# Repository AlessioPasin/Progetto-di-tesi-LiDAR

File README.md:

# Progetto di tesi: **Scheda per sensore LiDAR**

## Obiettivo:

Il seguente progetto riguarda una scheda per la gestione di due periferiche esterne: un laser ed un fotoricevitore.
L'obiettivo finale con la scheda è quello di realizzare un sensore LiDAR. Tale sensore viene utilizzato in diversi campi per misurare quella che è la distanza degli oggetti circostanti. Ne esistono di diverse tipologie e che sfruttano diversi principi fisici.

In questa applicazione viene utilizzato il **ToF** [*Time of Filght*], ossia il tempo che impiega il fascio laser per viaggare dalla sorgente all'oggetto e per poi tornare nuovamente alla fonte.

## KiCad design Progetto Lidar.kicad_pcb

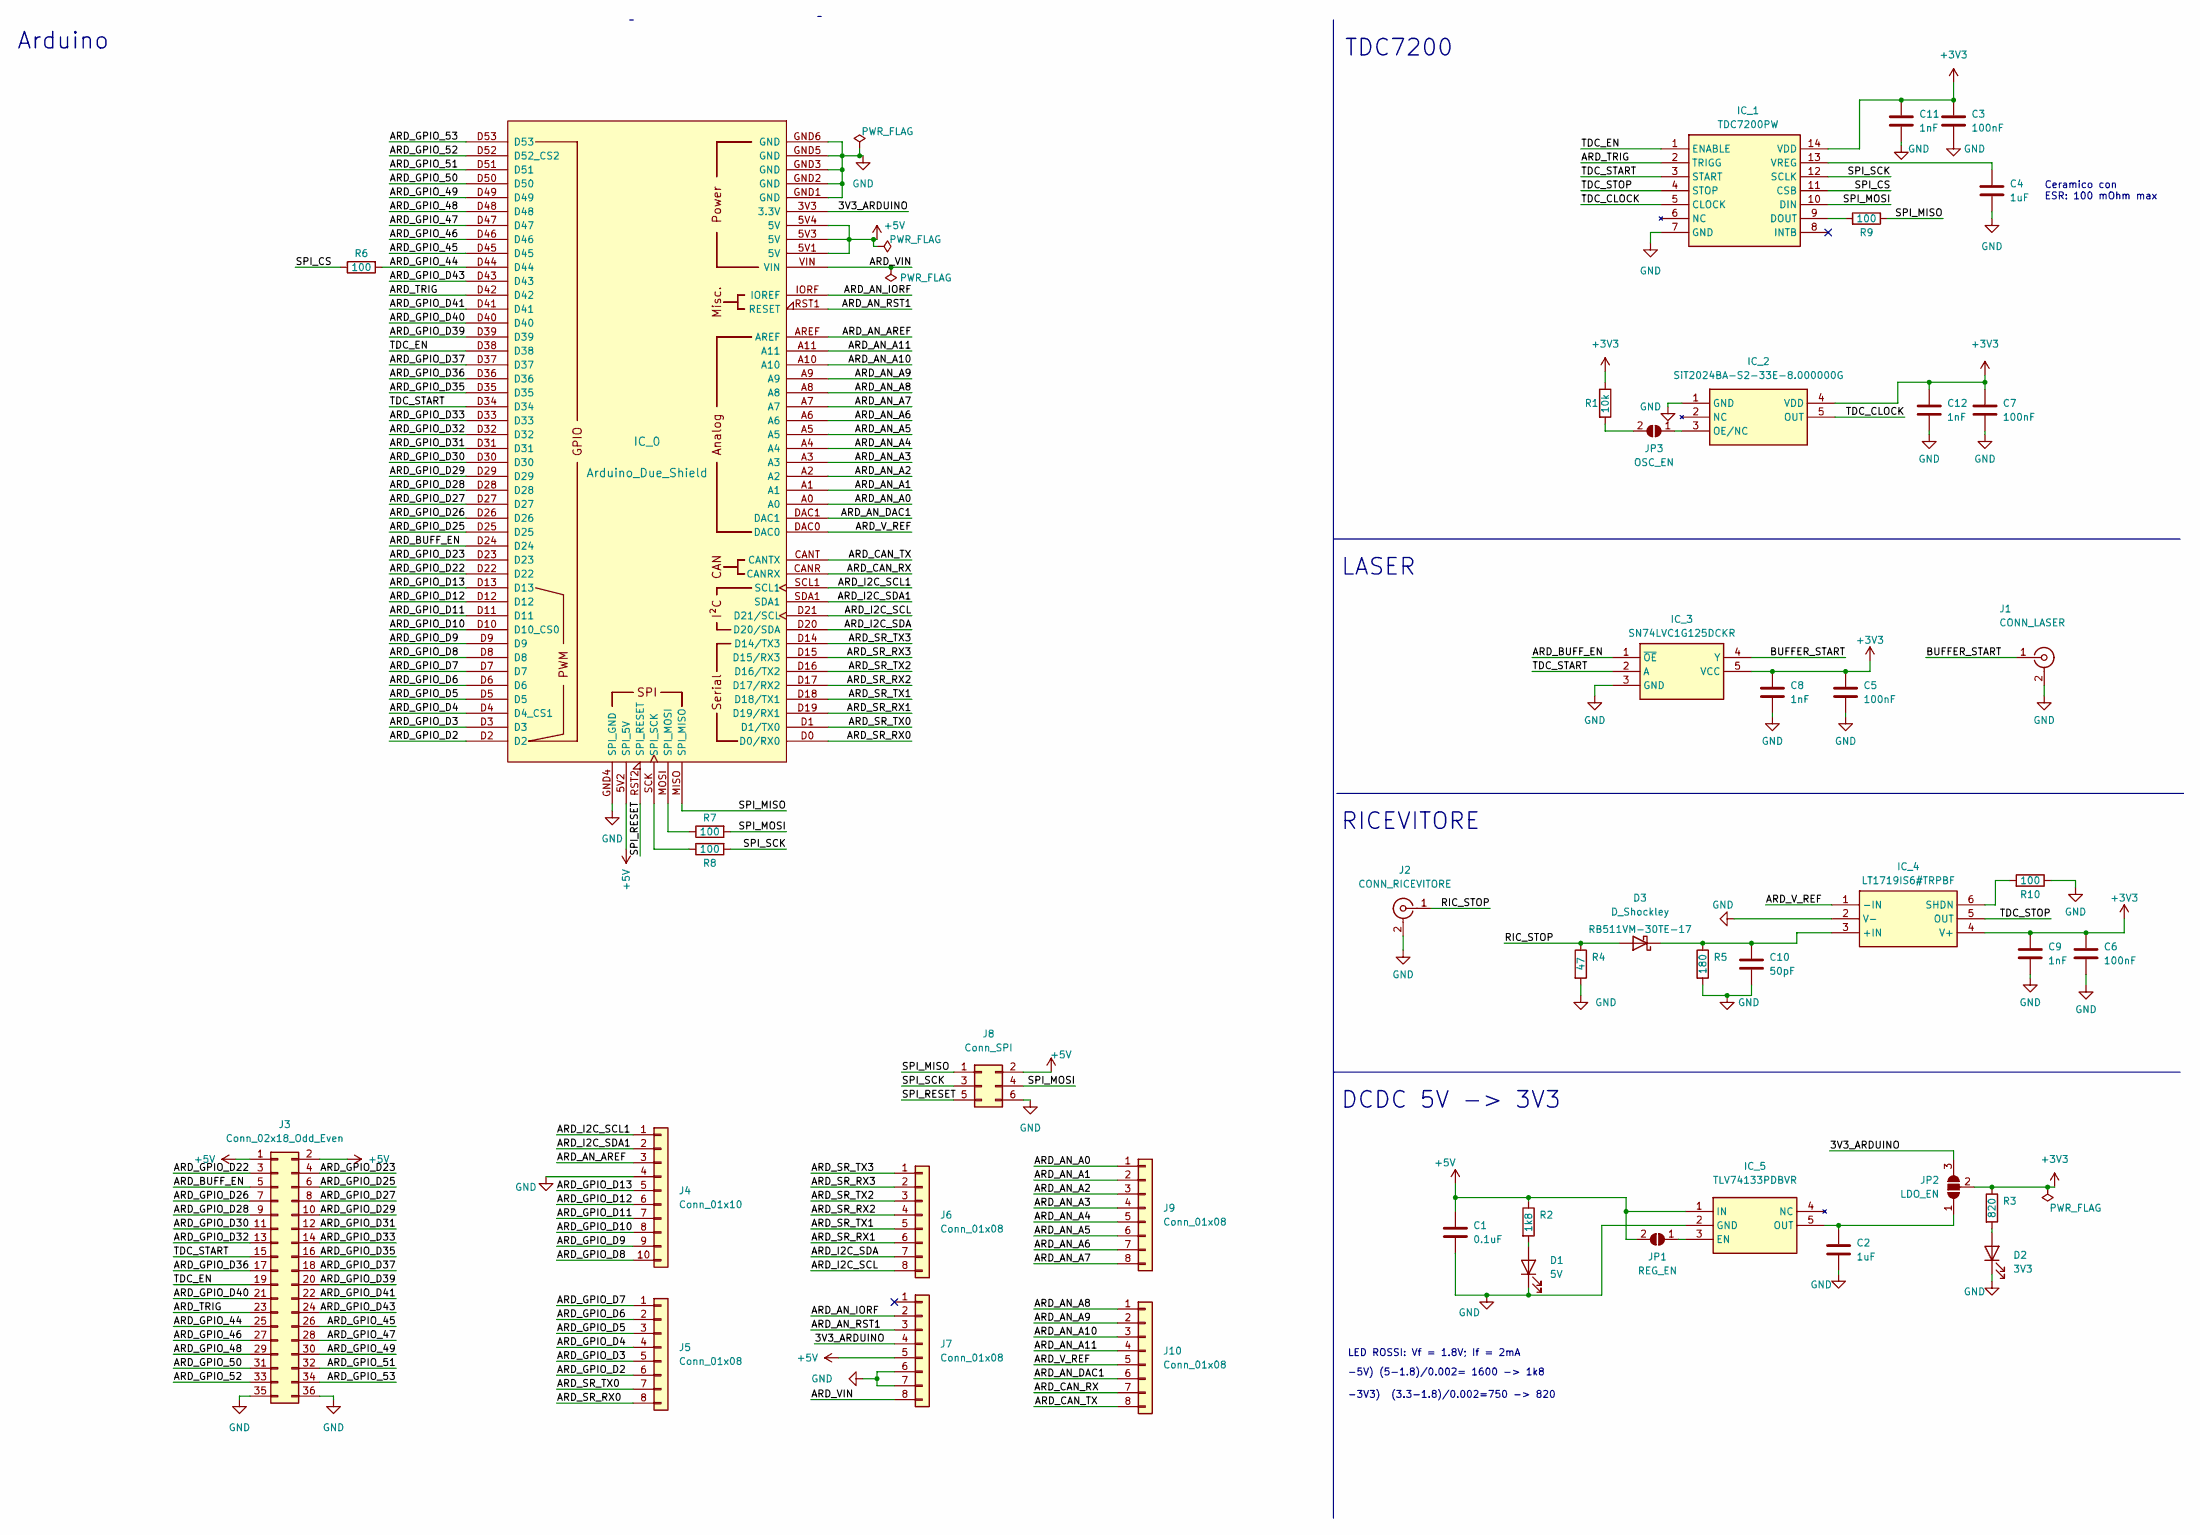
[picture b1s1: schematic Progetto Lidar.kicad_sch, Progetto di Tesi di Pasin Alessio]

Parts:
C1: 0.1uF; C_0805_2012Metric
C2, C4: 1uF; C_0805_2012Metric
C3, C5, C6, C7: 100nF; C_0805_2012Metric
C8, C9, C11, C12: 1nF; C_0805_2012Metric
C10: 50pF; C_0805_2012Metric
D1: 5V; LED_0805_2012Metric
D2: 3V3; LED_0805_2012Metric
D3: D_Shockley; RB511VM30TE17
IC_0: Arduino_Due_Shield
IC_1: TDC7200PW; SOP65P640X120-14N; Mouser Part Number 595-TDC7200PW
IC_2: SiT2024BA-S2-33E-8.000000G; SOT95P280X145-5N; Mouser Part Number 788-2024BA-S2-33E-8G
IC_3: SN74LVC1G125DCKR; SOT65P210X110-5N; Mouser Part Number 595-SN74LVC1G125DCKR
IC_4: LT1719IS6#TRPBF; SOT95P280X100-6N; Mouser Part Number 584-LT1719IS6#TRPBF
IC_5: TLV74133PDBVR; SOT95P280X145-5N; Mouser Part Number 595-TLV74133PDBVR
J1: CONN_LASER; SMA_Molex_73251-1153_EdgeMount_Horizontal
J2: CONN_RICEVITORE; SMA_Molex_73251-1153_EdgeMount_Horizontal
J3: Conn_02x18_Odd_Even; PinSocket_2x18_P2.54mm_Vertical
J4: Conn_01x10; PinSocket_1x10_P2.54mm_Vertical
J5, J6, J7, J9, J10: Conn_01x08; PinSocket_1x08_P2.54mm_Vertical
J8: Conn_SPI; PinSocket_2x03_P2.54mm_Vertical
JP1: REG_EN; SolderJumper-2_P1.3mm_Open_RoundedPad1.0x1.5mm
JP2: LDO_EN; SolderJumper-3_P1.3mm_Open_Pad1.0x1.5mm_NumberLabels
JP3: OSC_EN; SolderJumper-2_P1.3mm_Open_RoundedPad1.0x1.5mm
R1: 10k; R_0805_2012Metric
R2: 1k8; R_0805_2012Metric
R3: 820; R_0805_2012Metric
R4: 47; R_0805_2012Metric
R5: 180; R_0805_2012Metric
R6, R7, R8, R9, R10: 100; R_0805_2012Metric

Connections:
+3V3: C3.1, C5.1, C6.1, C7.1, C8.1, C9.1, C11.1, C12.1, IC_1.14 (VDD), IC_2.4 (VDD), IC_3.5 (VCC), IC_4.4 (V+), JP2.2 (C), R1.1, R3.1
+5V: C1.1, IC_0.5V1 (5V), IC_0.5V2 (SPI_5V), IC_0.5V3 (5V), IC_0.5V4 (5V), IC_5.1 (IN), J3.1, J3.2, J7.5, J8.2, JP1.2 (B), R2.1
/3V3_ARDUINO: IC_0.3V3 (3.3V), J7.4, JP2.3 (B)
/ARD_AN_A0: IC_0.A0, J9.1
/ARD_AN_A1: IC_0.A1, J9.2
/ARD_AN_A2: IC_0.A2, J9.3
/ARD_AN_A3: IC_0.A3, J9.4
/ARD_AN_A4: IC_0.A4, J9.5
/ARD_AN_A5: IC_0.A5, J9.6
/ARD_AN_A6: IC_0.A6, J9.7
/ARD_AN_A7: IC_0.A7, J9.8
/ARD_AN_A8: IC_0.A8, J10.1
/ARD_AN_A9: IC_0.A9, J10.2
/ARD_AN_A10: IC_0.A10, J10.3
/ARD_AN_A11: IC_0.A11, J10.4
/ARD_AN_AREF: IC_0.AREF, J4.3
/ARD_AN_DAC1: IC_0.DAC1, J10.6
/ARD_AN_IORF: IC_0.IORF (IOREF), J7.2
/ARD_AN_RST1: IC_0.RST1 (RESET), J7.3
/ARD_BUFF_EN: IC_0.D24, IC_3.1 (~OE), J3.5
/ARD_CAN_RX: IC_0.CANR (CANRX), J10.7
/ARD_CAN_TX: IC_0.CANT (CANTX), J10.8
/ARD_GPIO_44: IC_0.D44, J3.25, R6.2
/ARD_GPIO_45: IC_0.D45, J3.26
/ARD_GPIO_46: IC_0.D46, J3.27
/ARD_GPIO_47: IC_0.D47, J3.28
/ARD_GPIO_48: IC_0.D48, J3.29
/ARD_GPIO_49: IC_0.D49, J3.30
/ARD_GPIO_50: IC_0.D50, J3.31
/ARD_GPIO_51: IC_0.D51, J3.32
/ARD_GPIO_52: IC_0.D52 (D52_CS2), J3.33
/ARD_GPIO_53: IC_0.D53, J3.34
/ARD_GPIO_D2: IC_0.D2, J5.6
/ARD_GPIO_D3: IC_0.D3, J5.5
/ARD_GPIO_D4: IC_0.D4 (D4_CS1), J5.4
/ARD_GPIO_D5: IC_0.D5, J5.3
/ARD_GPIO_D6: IC_0.D6, J5.2
/ARD_GPIO_D7: IC_0.D7, J5.1
/ARD_GPIO_D8: IC_0.D8, J4.10
/ARD_GPIO_D9: IC_0.D9, J4.9
/ARD_GPIO_D10: IC_0.D10 (D10_CS0), J4.8
/ARD_GPIO_D11: IC_0.D11, J4.7
/ARD_GPIO_D12: IC_0.D12, J4.6
/ARD_GPIO_D13: IC_0.D13, J4.5
/ARD_GPIO_D22: IC_0.D22, J3.3
/ARD_GPIO_D23: IC_0.D23, J3.4
/ARD_GPIO_D25: IC_0.D25, J3.6
/ARD_GPIO_D26: IC_0.D26, J3.7
/ARD_GPIO_D27: IC_0.D27, J3.8
/ARD_GPIO_D28: IC_0.D28, J3.9
/ARD_GPIO_D29: IC_0.D29, J3.10
/ARD_GPIO_D30: IC_0.D30, J3.11
/ARD_GPIO_D31: IC_0.D31, J3.12
/ARD_GPIO_D32: IC_0.D32, J3.13
/ARD_GPIO_D33: IC_0.D33, J3.14
/ARD_GPIO_D35: IC_0.D35, J3.16
/ARD_GPIO_D36: IC_0.D36, J3.17
/ARD_GPIO_D37: IC_0.D37, J3.18
/ARD_GPIO_D39: IC_0.D39, J3.20
/ARD_GPIO_D40: IC_0.D40, J3.21
/ARD_GPIO_D41: IC_0.D41, J3.22
/ARD_GPIO_D43: IC_0.D43, J3.24
/ARD_I2C_SCL: IC_0.D21 (D21/SCL), J6.8
/ARD_I2C_SCL1: IC_0.SCL1, J4.1
/ARD_I2C_SDA: IC_0.D20 (D20/SDA), J6.7
/ARD_I2C_SDA1: IC_0.SDA1, J4.2
/ARD_SR_RX0: IC_0.D0 (D0/RX0), J5.8
/ARD_SR_RX1: IC_0.D19 (D19/RX1), J6.6
/ARD_SR_RX2: IC_0.D17 (D17/RX2), J6.4
/ARD_SR_RX3: IC_0.D15 (D15/RX3), J6.2
/ARD_SR_TX0: IC_0.D1 (D1/TX0), J5.7
/ARD_SR_TX1: IC_0.D18 (D18/TX1), J6.5
/ARD_SR_TX2: IC_0.D16 (D16/TX2), J6.3
/ARD_SR_TX3: IC_0.D14 (D14/TX3), J6.1
/ARD_TRIG: IC_0.D42, IC_1.2 (TRIGG), J3.23
/ARD_VIN: IC_0.VIN, J7.8
/ARD_V_REF: IC_0.DAC0, IC_4.1 (-IN), J10.5
/BUFFER_START: IC_3.4 (Y), J1.1 (In)
/RIC_STOP: D3.2 (A), J2.1 (In), R4.1
/SPI_CS: IC_1.11 (CSB), R6.1
/SPI_MISO: IC_0.MISO (SPI_MISO), J8.1, R9.1
/SPI_MOSI: IC_1.10 (DIN), J8.4, R7.2
/SPI_RESET: IC_0.RST2 (SPI_RESET), J8.5
/SPI_SCK: IC_1.12 (SCLK), J8.3, R8.2
/TDC_CLOCK: IC_1.5 (CLOCK), IC_2.5 (OUT)
/TDC_EN: IC_0.D38, IC_1.1 (ENABLE), J3.19
/TDC_START: IC_0.D34, IC_1.3 (START), IC_3.2 (A), J3.15
/TDC_STOP: IC_1.4 (STOP), IC_4.5 (OUT)
GND: C1.2, C2.2, C3.2, C4.2, C5.2, C6.2, C7.2, C8.2, C9.2, C10.2, C11.2, C12.2, D1.1 (K), D2.1 (K), IC_0.GND1 (GND), IC_0.GND2 (GND), IC_0.GND3 (GND), IC_0.GND4 (SPI_GND), IC_0.GND5 (GND), IC_0.GND6 (GND), IC_1.7 (GND), IC_2.1 (GND), IC_3.3 (GND), IC_4.2 (V-), IC_5.2 (GND), J1.2 (Ext), J2.2 (Ext), J3.35, J3.36, J4.4, J7.6, J7.7, J8.6, R4.2, R5.2, R10.1
unnamed: C2.1, IC_5.5 (OUT), JP2.1 (A)
unnamed: C4.1, IC_1.13 (VREG)
unnamed: C10.1, D3.1 (K), IC_4.3 (+IN), R5.1
unnamed: D1.2 (A), R2.2
unnamed: D2.2 (A), R3.2
unnamed: IC_0.MOSI (SPI_MOSI), R7.1
unnamed: IC_0.SCK (SPI_SCK), R8.1
unnamed: IC_1.9 (DOUT), R9.2
unnamed: IC_2.3 (OE/NC), JP3.1 (A)
unnamed: IC_4.6 (SHDN), R10.2
unnamed: IC_5.3 (EN), JP1.1 (A)
unnamed: JP3.2 (B), R1.2

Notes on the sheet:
RICEVITORE
-5V) (5-1.8)/0.002= 1600 -> 1k8 -3V3) (3.3-1.8)/0.002=750 -> 820
DCDC 5V -> 3V3
Arduino
LED ROSSI: Vf = 1.8V; If = 2mA
LASER
TDC7200
Ceramico con ESR: 100 mOhm max

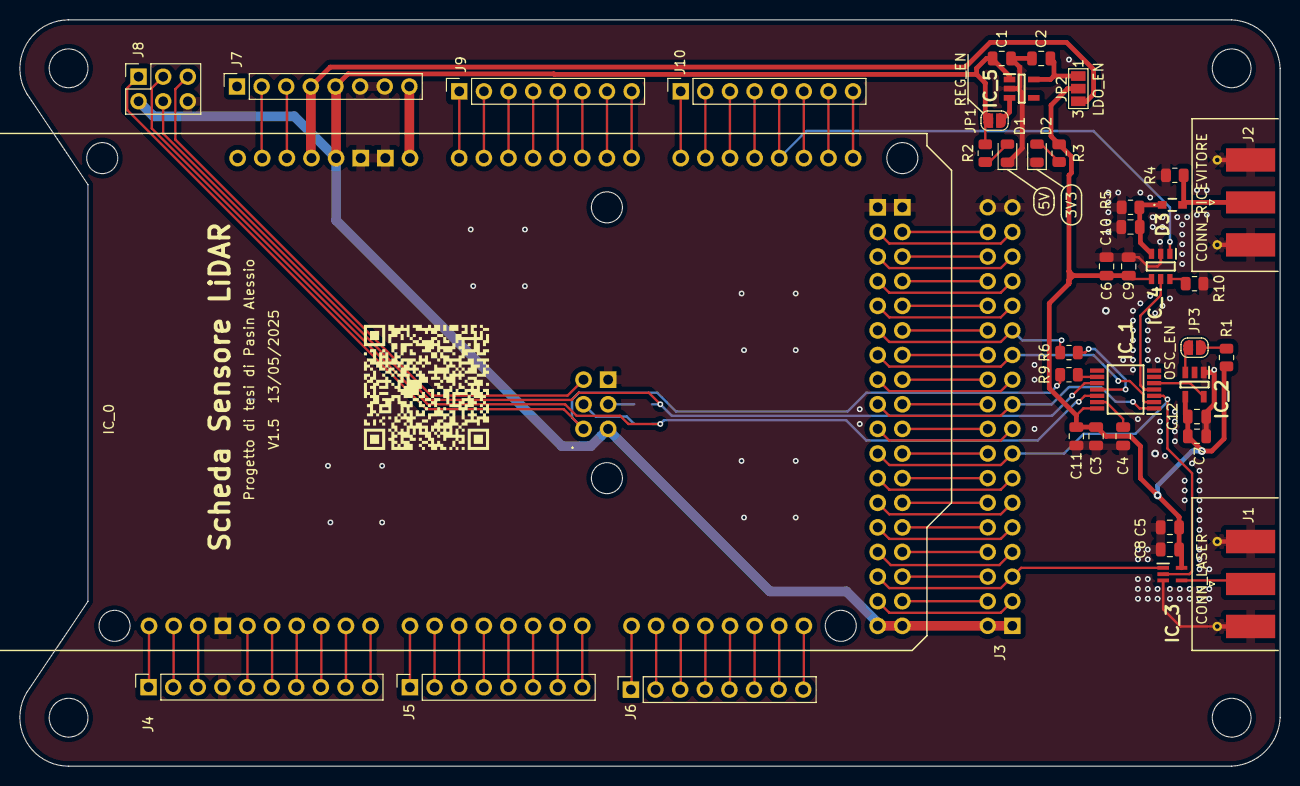
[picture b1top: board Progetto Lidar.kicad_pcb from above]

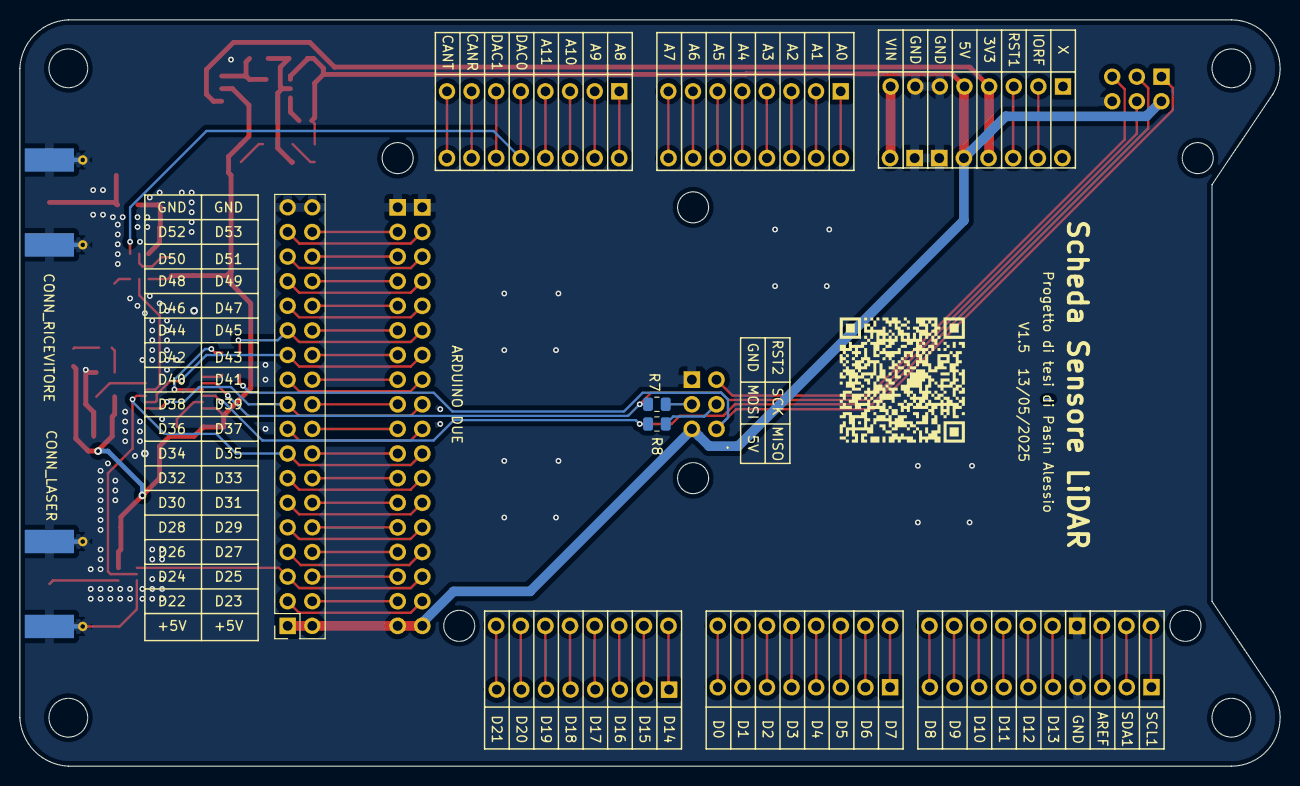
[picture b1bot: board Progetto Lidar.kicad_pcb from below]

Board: 2 copper layers, 130.0 x 77.0 mm, 44 parts (4 on the bottom side), 101 nets.

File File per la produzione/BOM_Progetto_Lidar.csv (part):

"Source:","D:\Documenti_A\Università\Corsi\Tesi\Progetto Kicad Lidar\Progetto Lidar.kicad_sch"
"Date:","12/05/2025 09:19:33"
"Tool:","Eeschema (6.0.10)"
"Generator:","C:\Program Files\KiCad\6.0\bin\scripting\plugins/bom_csv_grouped_by_value.py"
"Component Count:","44"

"Individual Components:"

"Item","Qty","Reference(s)","Value","LibPart","Footprint","Datasheet","Datasheet_1","Dettagli","Footprint_1","Height","Manufacturer_Name","Manufacturer_Part_Number","Modello","Mouser Part Number","Mouser Price/Stock","Reference_1","Value_1"
"","","C1","0.1uF","Device:C","Capacitor_SMD:C_0805_2012Metric","~","","","","","","","","","","",""
"","","C2","1uF","Device:C","Capacitor_SMD:C_0805_2012Metric","~","","","","","","","","","","",""
"","","C3","100nF","Device:C","Capacitor_SMD:C_0805_2012Metric","~","","","","","","","","","","",""
"","","C4","1uF","Device:C","Capacitor_SMD:C_0805_2012Metric","~","","Ceramico con ESR: 100 mOhm max","","","","","","","","",""
"","","C5","100nF","Device:C","Capacitor_SMD:C_0805_2012Metric","~","","","","","","","","","","",""
"","","C6","100nF","Device:C","Capacitor_SMD:C_0805_2012Metric","~","","","","","","","","","","",""
"","","C7","100nF","Device:C","Capacitor_SMD:C_0805_2012Metric","~","","","","","","","","","","",""
"","","C8","1nF","Device:C","Capacitor_SMD:C_0805_2012Metric","~","","","","","","","","","","",""
"","","C9","1nF","Device:C","Capacitor_SMD:C_0805_2012Metric","~","","","","","","","","","","",""
"","","C10","50pF","Device:C","Capacitor_SMD:C_0805_2012Metric","~","","","","","","","","","","",""
"","","C11","1nF","Device:C","Capacitor_SMD:C_0805_2012Metric","~","","","","","","","","","","",""
"","","C12","1nF","Device:C","Capacitor_SMD:C_0805_2012Metric","~","","","","","","","","","","",""
"","","D1","5V","Device:LED","LED_SMD:LED_0805_2012Metric","https://www.mouser.it/ProductDetail/ROHM-Semiconductor/SML-2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","","","","","","","","","","",""
"","","D2","3V3","Device:LED","LED_SMD:LED_0805_2012Metric","~","","","","","","","","","","",""
"","","D3","D_Shockley","Device:D_Schottky","Libreria_componenti_footprint:RB511VM30TE17","Datasheet/rb511vm-30te-17-e.pdf","","","","","","","RB511VM-30TE-17","","","",""
"","","IC_0","Arduino_Due_Shield","arduino-library:Arduino_Due_Shield","arduino-library:Arduino_Due_Shield","https://docs.arduino.cc/hardware/due","","","","","","","","","","",""
"","","IC_1","TDC7200PW","Libreria_componenti:TDC7200PW","Libreria_componenti_footprint:SOP65P640X120-14N","Datasheet/tdc7200.pdf","http://www.ti.com/lit/ds/symlink/tdc7200.pdf","","SOP65P640X120-14N","1.2","Texas Instruments","TDC7200PW","","595-TDC7200PW","https://www.mouser.co.uk/ProductDetail/Texas-Instruments/TDC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","IC","TDC7200PW"
"","","IC_2","SiT2024BA-S2-33E-8.000000G","Libreria_componenti:SiT2024BA-S2-33E-8.000000G","Libreria_componenti_footprint:SOT95P280X145-5N","Datasheet/SiT2024B.pdf","https://www.mouser.it/datasheet/2/371/SiT2024B-datasheet-111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","","SOT95P280X145-5N","1.45","SiTime","SiT2024BA-S2-33E-8.000000G","","788-2024BA-S2-33E-8G","https://www.mouser.co.uk/ProductDetail/SiTime/SiT2024BA-S2-3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","Y","SiT2024BA-S2-33E-8.000000G"
"","","IC_3","SN74LVC1G125DCKR","Libreria_componenti:SN74LVC1G125DCKR","Libreria_componenti_footprint:SOT65P210X110-5N","Datasheet/sn74lvc1g125.pdf","https://datasheet.datasheetarchive.com/originals/distributor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","","SOT65P210X110-5N","1.1","Texas Instruments","SN74LVC1G125DCKR","","595-SN74LVC1G125DCKR","https://www.mouser.co.uk/ProductDetail/Texas-Instruments/SN7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","IC","SN74LVC1G125DCKR"
"","","IC_4","LT1719IS6#TRPBF","Libreria_componenti:LT1719IS6#TRPBF","Libreria_componenti_footprint:SOT95P280X100-6N","Datasheet/LT1719IS6.pdf","https://www.analog.com/media/en/technical-documentation/data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","","SOT95P280X100-6N","1","Analog Devices","LT1719IS6#TRPBF","","584-LT1719IS6#TRPBF","https://www.mouser.co.uk/ProductDetail/Analog-Devices/LT1719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","IC","LT1719IS6#TRPBF"
"","","IC_5","TLV74133PDBVR","Libreria_componenti:TLV74133PDBVR","Libreria_componenti_footprint:SOT95P280X145-5N","Datasheet/tlv741p.pdf","","","","1.45","Texas Instruments","TLV74133PDBVR","","595-TLV74133PDBVR","https://www.mouser.co.uk/ProductDetail/Texas-Instruments/TLV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","",""
"","","J1","CONN_LASER","Connector:Conn_Coaxial","Connector_Coaxial:SMA_Molex_73251-1153_EdgeMount_Horizontal"," ~","","","","","","","","","","",""
"","","J2","CONN_RICEVITORE","Connector:Conn_Coaxial","Connector_Coaxial:SMA_Molex_73251-1153_EdgeMount_Horizontal"," ~","","","","","","","","","","",""
"","","J3","Conn_02x18_Odd_Even","Connector_Generic:Conn_02x18_Odd_Even","Connector_PinSocket_2.54mm:PinSocket_2x18_P2.54mm_Vertical","~","","","","","","","","","","",""
"","","J4","Conn_01x10","Connector_Generic:Conn_01x10","Connector_PinSocket_2.54mm:PinSocket_1x10_P2.54mm_Vertical","~","","","","","","","","","","",""
"","","J5","Conn_01x08","Connector_Generic:Conn_01x08","Connector_PinSocket_2.54mm:PinSocket_1x08_P2.54mm_Vertical","~","","","","","","","","","","",""
"","","J6","Conn_01x08","Connector_Generic:Conn_01x08","Connector_PinSocket_2.54mm:PinSocket_1x08_P2.54mm_Vertical","~","","","","","","","","","","",""
"","","J7","Conn_01x08","Connector_Generic:Conn_01x08","Connector_PinSocket_2.54mm:PinSocket_1x08_P2.54mm_Vertical","~","","","","","","","","","","",""
"","","J8","Conn_SPI","Connector_Generic:Conn_02x03_Odd_Even","Connector_PinSocket_2.54mm:PinSocket_2x03_P2.54mm_Vertical","~","","","","","","","","","","",""
"","","J9","Conn_01x08","Connector_Generic:Conn_01x08","Connector_PinSocket_2.54mm:PinSocket_1x08_P2.54mm_Vertical","~","","","","","","","","","","",""
"","","J10","Conn_01x08","Connector_Generic:Conn_01x08","Connector_PinSocket_2.54mm:PinSocket_1x08_P2.54mm_Vertical","~","","","","","","","","","","",""
"","","JP1","REG_EN","Jumper:SolderJumper_2_Open","Jumper:SolderJumper-2_P1.3mm_Open_RoundedPad1.0x1.5mm","~","","","","","","","","","","",""
"","","JP2","LDO_EN","Jumper:SolderJumper_3_Open","Jumper:SolderJumper-3_P1.3mm_Open_Pad1.0x1.5mm_NumberLabels","~","","","","","","","","","","",""
"","","JP3","OSC_EN","Jumper:SolderJumper_2_Open","Jumper:SolderJumper-2_P1.3mm_Open_RoundedPad1.0x1.5mm","~","","","","","","","","","","",""
"","","R1","10k","Device:R","Resistor_SMD:R_0805_2012Metric","~","","","","","","","","","","",""
"","","R2","1k8","Device:R","Resistor_SMD:R_0805_2012Metric","~","","","","","","","","","","",""
"","","R3","820","Device:R","Resistor_SMD:R_0805_2012Metric","~","","","","","","","","","","",""
"","","R4","47","Device:R","Resistor_SMD:R_0805_2012Metric","~","","","","","","","","","","",""
"","","R5","180","Device:R","Resistor_SMD:R_0805_2012Metric","~","","","","","","","","","","",""
"","","R6","100","Device:R","Resistor_SMD:R_0805_2012Metric","~","","","","","","","","","","",""
"","","R7","100","Device:R","Resistor_SMD:R_0805_2012Metric","~","","","","","","","","","","",""
"","","R8","100","Device:R","Resistor_SMD:R_0805_2012Metric","~","","","","","","","","","","",""
"","","R9","100","Device:R","Resistor_SMD:R_0805_2012Metric","~","","","","","","","","","","",""
"","","R10","100","Device:R","Resistor_SMD:R_0805_2012Metric","~","","","","","","","","","","",""



"Collated Components:"

"Item","Qty","Reference(s)","Value","LibPart","Footprint","Datasheet","Datasheet_1","Dettagli","Footprint_1","Height","Manufacturer_Name","Manufacturer_Part_Number","Modello","Mouser Part Number","Mouser Price/Stock","Reference_1","Value_1"
"1","1","C1","0.1uF","Device:C","Capacitor_SMD:C_0805_2012Metric","~","","","","","","","","","","",""
"2","2","C2, C4","1uF","Device:C","Capacitor_SMD:C_0805_2012Metric","~","","Ceramico con ESR: 100 mOhm max","","","","","","","","",""
"3","4","C3, C5, C6, C7","100nF","Device:C","Capacitor_SMD:C_0805_2012Metric","~","","","","","","","","","","",""
"4","4","C8, C9, C11, C12","1nF","Device:C","Capacitor_SMD:C_0805_2012Metric","~","","","","","","","","","","",""
"5","1","C10","50pF","Device:C","Capacitor_SMD:C_0805_2012Metric","~","","","","","","","","","","",""
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
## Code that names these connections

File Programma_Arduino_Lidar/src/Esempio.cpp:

#include <Arduino.h>
#include <SPI.h>

//Definiamo alcune costanti che verranno utilizzate in seguito:

const int CS = 44;                //Pin di selezione del TDC. Viene utilizzato nella comunicazione SPI
const int TDC_EN = 38;            //Pin di ENABLE del TDC. Da inizializzare dopo l'accensione
const int ARD_TRIGG = 42;         //Pin di TRIGGER del TDC. Da inizializzare dopo l'accensione
const int TDC_START = 34;         //Pin di invio comando di partenza della misurazione
const int ARD_BUFF_EN = 24;       //Pin di ENABLE del BUFFER
const int ARD_V_REF = DAC0;       //Pin di generazione della tensione di riferimento

const int WRITE = 1;
const int READ = 0;

int mod_misurazione = '0';    // Permette di avviare la modalità di misurazione del dispositivo
int s = 0;                    // Variabile per la lettura dei registri di configurazione

const int CalibPeriod = 10 ;    //Numero di cicli di calibrazione

const int ClockFreq = 16;        //Frequenza del clock in MHz (Noi in realtà avremmo 16MHz)

const double velLuce = 299792458.0 ; //Velocità espressa in m/s

//===========================================================================================================




void writeTDC(byte thisRegister, byte autoIncrement, byte thisValue)  //Si crea la funzione per l'invio dei dati dall'arduino al TDC:
{
  unsigned int sendDetails = (autoIncrement << 7) | (WRITE << 6) | (thisRegister) ; //Si crea il byte da 8 bit per il "Command field"
  Serial.println(sendDetails, BIN);
  
  digitalWrite(CS, LOW);              //Si inizializza la fase di scrittura al dispositivo

  SPI.transfer(sendDetails);          //Si inviano le specifiche della comunicazione
  SPI.transfer(thisValue);            //Si invia il valore da inserire nel registro
  
  digitalWrite(CS, HIGH);             //Si termina la fase di scrittura al dispositivo
}




unsigned int readTDC(byte thisRegister, byte autoIncrement, int length)   //Si crea la funzione per la lettura dei dati con autoincremento dal TDC all'Arduino:
{
  if (length < 1 || length > 3) return 0;

  digitalWrite(CS, LOW);

  // Comando: [Auto-Inc][R/W][Addr(6 bit)]
  unsigned int command = (autoIncrement << 7) | (READ << 6) | (thisRegister);
  Serial.println(command, BIN);
  SPI.transfer(command);


  // Legge i dati da MSB a LSB
  unsigned int value = 0b000000000000000000000000;
  for (int i = 0; i < length; i++) {
    value = (value << 8) | SPI.transfer(0x00);
    Serial.println(value, BIN);
  }
  digitalWrite(CS, HIGH);
  return value;
}


void printDouble( double val, unsigned int precision){  //Funzione di stampa dei valori double

   Serial.print (int(val));  //prints the int part
    Serial.print("."); // print the decimal point
    unsigned int frac;
    if(val >= 0)
      frac = (val - int(val)) * precision;
    else
       frac = (int(val)- val ) * precision;
    int frac1 = frac;
    while( frac1 /= 10 )
        precision /= 10;
    precision /= 10;
    while(  precision /= 10)
        Serial.print("0");

    Serial.println(frac,DEC) ;
} 


//===============================================================================================================






void setup() {
  SPI.begin();
  SPI.beginTransaction(SPISettings(14000000, MSBFIRST, SPI_MODE0));
  Serial.begin(115200);
  Serial.println("Comunicazione inizializzata.");


  pinMode(CS, OUTPUT);                //Inizializziamo tutti i pin secondo la loro funzione
  pinMode(TDC_EN, OUTPUT);
  pinMode(ARD_TRIGG, INPUT);
  pinMode(TDC_START, OUTPUT);
  pinMode(ARD_BUFF_EN, OUTPUT);
  pinMode(ARD_V_REF, OUTPUT);



  digitalWrite(TDC_EN, HIGH);             //Abilitiamo il TDC
  digitalWrite(ARD_BUFF_EN, LOW);        //Abilitiamo il BUFFER


  
  Serial.println("Scrivo i registri di configurazione:");       //[Registro, Autoincremento, valore]
  writeTDC(0x00, 0, 0x81);        //Definiamo i parametri del primo registro come: 01000000 (Pag: 25 datasheet)
  writeTDC(0x01, 0, 0x40);        //Definiamo i parametri del secondo registro come: 01000001 (Pag: 26 datasheet)
  // writeTDC(0x08, 0, 0x03);        
  // writeTDC(0x09, 0, 0x04);        
  
  delay(1500);
}



void loop() {

  if(s == 0){
    
    Serial.println("=====CONFIG 1======");
    int config1 = readTDC(0x00, 1, 1);        //[Registro, Autoincremento, Lunghezza]
    Serial.print("Valore della configurazione 1:");
    Serial.println(config1, BIN);
    
    
    Serial.println("=====CONFIG 2======");
    int config2 = readTDC(0x01, 1, 1);
    Serial.print("Valore della configurazione 2:");
    Serial.println(config2, BIN);
    
    
    Serial.println("=====INT_STATUS======");
    unsigned int intStatus = readTDC(0x02, 1, 1);
    Serial.print("Valore dell'INT status:");
    Serial.println(intStatus, BIN);
    
    
    Serial.println("=====INT_MASK======");
    unsigned int intMask = readTDC(0x03, 1, 1);
    Serial.print("Valore dell'INT mask:");
    Serial.println(intMask, BIN);
    
    s++;
  }
  
  
  digitalWrite(13, LOW);
  analogWrite(ARD_V_REF, 15);    //Impostiamo una tensione di riferimento da 0.1V
  mod_misurazione=Serial.read();                  //Acquisiamo il comando di avvio misurazione da tastiera. Premere 0 = Nessuna misurazione. Premere 1 = Avvio misurazione
  
  if (mod_misurazione == '1')         //Entriamo nel loop per effettuare la misurazione
  {
    Serial.println("<ESEGUO LA MISURAZIONE>");
    digitalWrite(TDC_START, HIGH);
    delay(1);
    digitalWrite(TDC_START, LOW);
    delay(1);
    // digitalWrite(TDC_START, HIGH);
    // delay(1);
    // digitalWrite(TDC_START, LOW);
    // delay(13);
  }
  
  
  delay(500);
  digitalWrite(13, HIGH);
  
  
  Serial.println("=====CALIBRATION1======");
  unsigned int calib1 = readTDC(0x1B, 1, 3);
  Serial.print("Valore del calibration 1:");
  Serial.println(calib1, BIN);
  
  Serial.println("=====CALIBRATION2======");
  unsigned int calib2 = readTDC(0x1C, 1, 3);
  Serial.print("Valore del calibration 2:");
  Serial.println(calib2, BIN);
  
  
  
  Serial.println("=====TIME 1======");
  unsigned int time1 = readTDC(0x10, 1, 3);
  Serial.print("Valore del registro TIME 1:");
  Serial.println(time1, BIN);
  
  // Serial.println("=====CLOCK COUNT 1======");
  // unsigned int clockCount1 = readTDC(0x11, 1, 3);
  // Serial.print("Valore del registro CLOCK COUNT 1:");
  // Serial.println(clockCount1, BIN);
  
  
  
  // Serial.println("=====TIME 2======");
  // unsigned int time2 = readTDC(0x12, 1, 3);
  // Serial.print("Valore del registro TIME 2:");
  // Serial.println(time2, BIN);
  
  // Serial.println("=====CLOCK COUNT 2======");
  // unsigned int clockCount2 = readTDC(0x13, 1, 3);
  // Serial.print("Valore del registro CLOCK COUNT 2:");
  // Serial.println(clockCount2, BIN);
  
  
  if (mod_misurazione == '1')
  {
    
    long double calCount = (double(calib2 - calib1))/(CalibPeriod - 1) ;
    // Serial.print("CalCount1:");
    // printDouble(calCount,10000);
    
    // Serial.println(ClockFreq *pow(10.0,6.0));
    long double normLSB = ((1.0/double((ClockFreq *pow(10,6)))) * (1.0/calCount));
    // long double normLSBnano = ((1.0/double((ClockFreq *pow(10,6)))) * (1.0/calCount)*pow(10,9));
    // Serial.print("normLSBnano1:");
    // printDouble(normLSBnano,100);
    
    double TOF1 = time1 * normLSB;
    double TOF1nano = time1 * normLSB * pow(10,9);      //CORRETTO: Tempo espresso in nanosecondi [ns]
    Serial.print("TOF1nano [ns]:");
    printDouble(TOF1nano,100);
    
    double distanza = (velLuce * TOF1)/2 ; 
    Serial.print("Distanza1 [m]:");
    printDouble(distanza,100);
    mod_misurazione = '0';    //Facciamo in modo da eseguire un unica chiamata alla misurazione
}



Serial.println("================================================");
delay(9000);
}

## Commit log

2025-03-17 Primo commit con lo schematico quasi completato
2025-03-17 Finito lo schematico e aggiunto modelli 3D
2025-03-19 Finito il layout della prima versione della scheda
2025-03-20 Specchiato Arduino per funzionare con connettori femmina
2025-03-25 Apportate modifiche dopo incontro con prof. 25.03.2025
2025-03-25 Finito layout e schematico. Aggiornato Silkscreen
2025-03-26 Aggiunto pinou di Arduino su silkscreen
2025-03-26 Modificato il Readme
2025-04-04 Creata simulazione LT1719
2025-04-11 Corretto simulazione, aggiunto circuito di condizionamento del segnale e modificato il layout
2025-04-13 Sistemato alcuni errori di circuito, aggiunto resistenze per SPI, aggiunto condensatori di filtraggio
2025-04-15 Ulteriori modifiche
2025-04-27 Corretto collegamento TDC_START
2025-05-12 Aggiunto vias nei circuiti veloci, rimosso piste GND, organizzato cartella e file, generato i file per la produzione
2025-05-12 Sistemato file BOM
2025-05-12 Sistemata la BOM
2025-05-13 Corretto connessione TDC ENABLE
2025-05-13 Rifatti i file per la produzione, modificato diametro fori, aggiunto scritte sul retro
2025-07-18 Aggiunta programma per Arduino
2025-07-18 Scrittura e lettura registri da 8 bit funzionante
2025-07-18 Ulteriori modifiche. Bisogna verificare il funzionamento dell'oscillatore
2025-07-21 Creato funzioni di conversione utilizzando gli esempi forniti dal datasheet
2025-07-21 Realizzato il codice per la conversione dai valori nel registro ad un effettivo valore in metri, sempre sfruttando gli esempi del datasheet
2025-07-21 Corretto file principale per la lettura dei registri del TDC
2025-07-24 Versione del programma successivamente alla lettura del segnale
2025-07-24 Programma funzionante sulla singola misurazione
2025-07-24 Programma sviluppato secondo switch-case, funzionante e testato
2025-07-25 Versione corretta del programma. Era sbagliata la formula per il calcolo del TOF durante la seconda modalità di misurazione
